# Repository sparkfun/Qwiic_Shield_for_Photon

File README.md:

SparkFun Qwiic Shield for Photon
========================================

[*Qwiic Shield for Photon*](https://www.sparkfun.com/products/14477)

This is a board that connects the I<sup>2</sup>C bus on the Photon to 4 Qwiic connectors.

Repository Contents
-------------------

* **/Hardware** - Eagle design files (.brd, .sch)
* **/Production** - Production panel files (.brd)

Documentation
--------------
* **[Hookup Guide](https://learn.sparkfun.com/tutorials/qwiic-shield-for-arduino--photon-hookup-guide)** - Basic hookup guide for the Qwiic Shield for Photon.

License Information
-------------------

This product is _**open source**_! 

Please review the LICENSE.md file for license information. 

If you have any questions or concerns on licensing, please contact techsupport@sparkfun.com.

Distributed as-is; no warranty is given.

- Your friends at SparkFun.

_<COLLABORATION CREDIT>_

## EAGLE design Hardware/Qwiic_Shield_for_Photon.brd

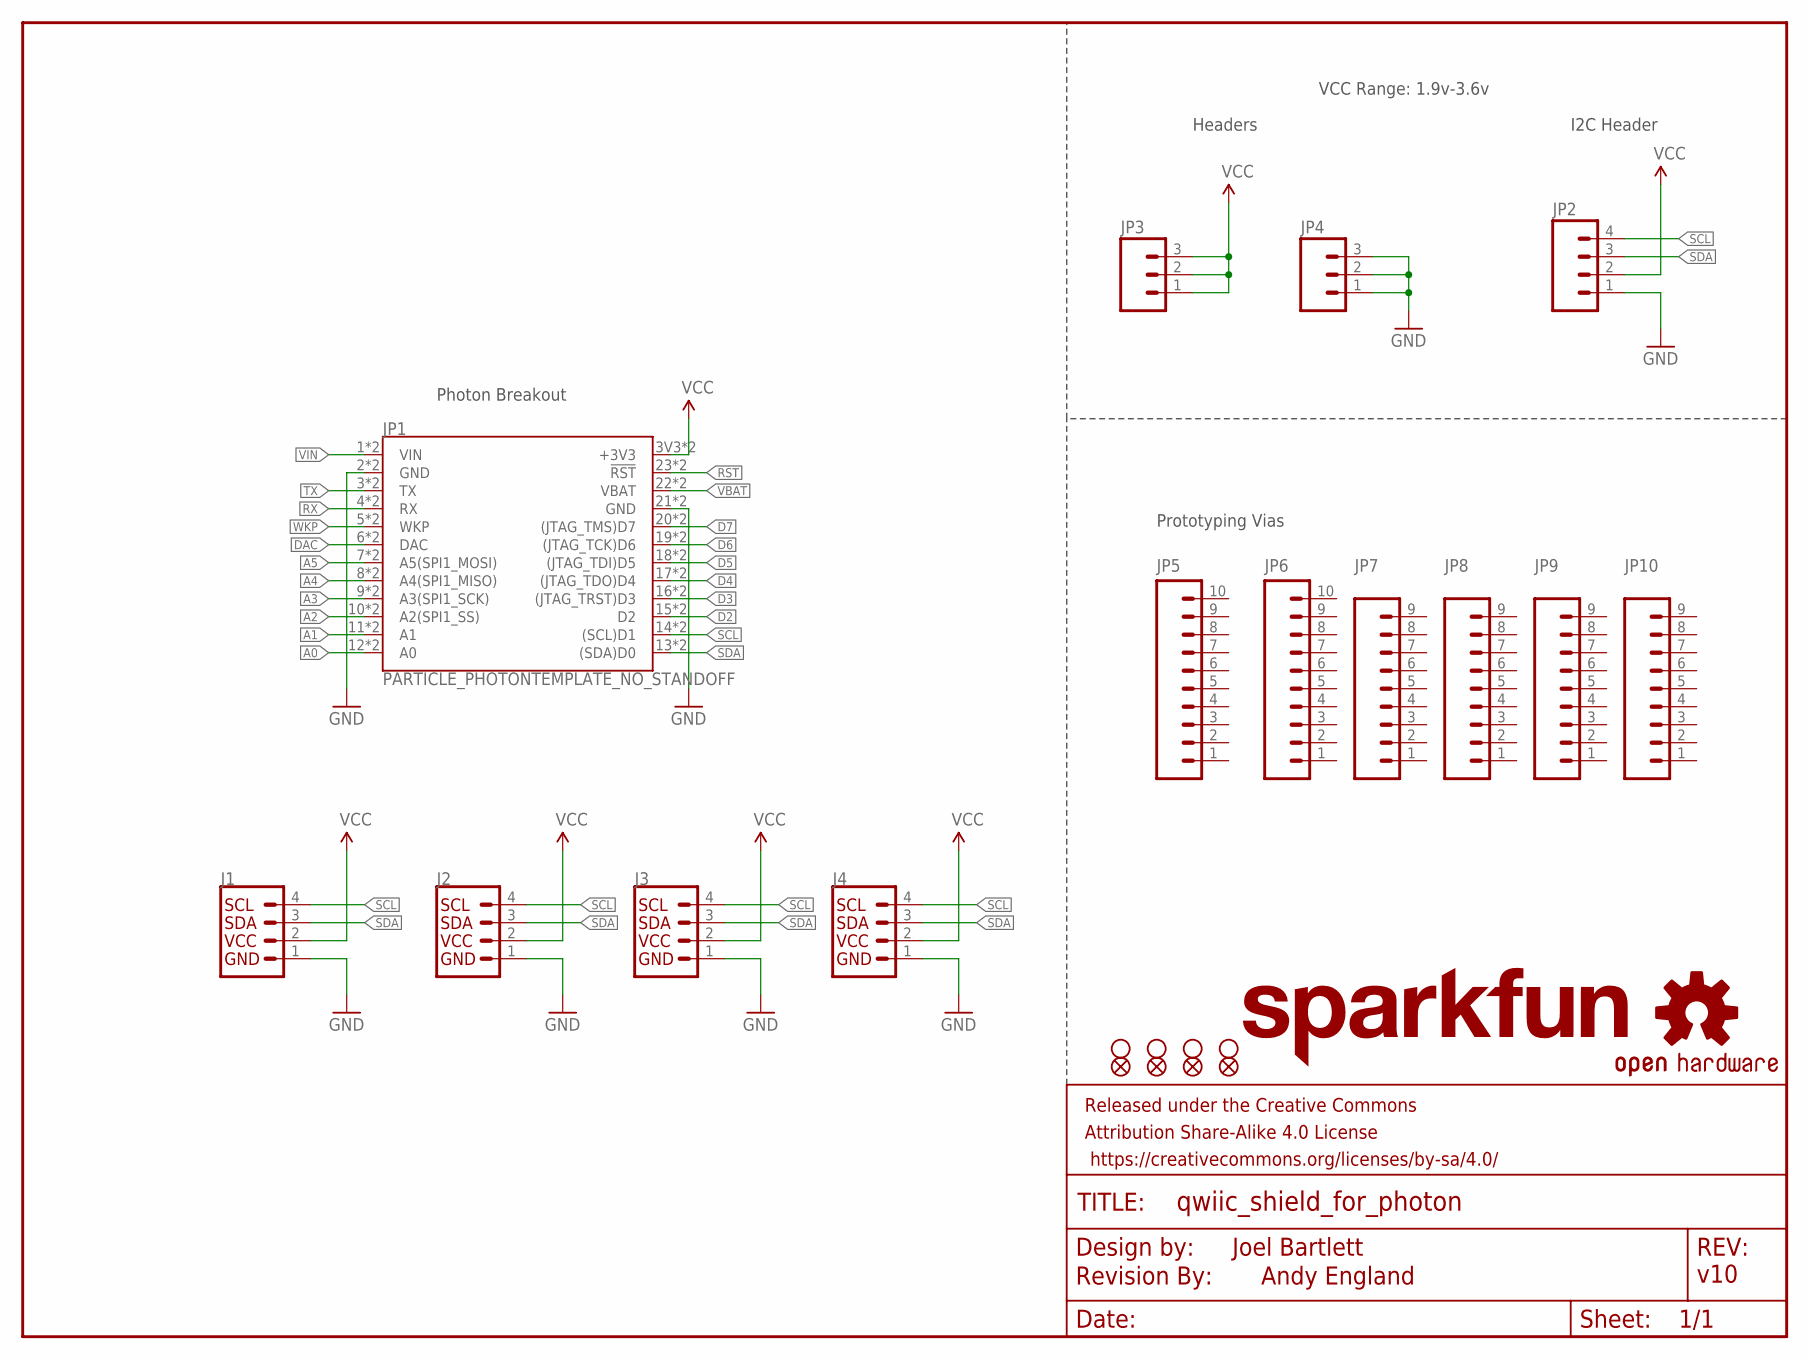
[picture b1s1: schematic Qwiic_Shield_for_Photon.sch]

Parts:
FD1, FD2, FD3, FD4: FIDUCIALUFIDUCIAL; FIDUCIAL-MICRO
FRAME1: FRAME-LETTER; CREATIVE_COMMONS
H1, H2, H3, H4: STAND-OFF
J1, J2, J3: QWIIC_CONNECTORJS-1MM; 1X04_1MM_RA
J4: I2C_STANDARDJS-1MM; 1X04_1MM_RA
JP1: PARTICLE_PHOTONTEMPLATE_NO_STANDOFF; PARTICLE_PHOTON_TEMPLATE_NO_STANDOFF
JP2: M04PTH; 1X04
JP3, JP4: M03PTH; 1X03
JP5, JP6: M10NO_SILK_PTH_FEMALE; 1X10_NO_SILK
JP7, JP8, JP9, JP10: M09NO_SILK; 1X09_NO_SILK
LOGO1: OSHW-LOGOM; OSHW-LOGO-M
LOGO2: REVISION
U$4: SFE_LOGO_NAME.1_INCH; SFE_LOGO_NAME_.1

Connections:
A0: JP1.12 (A0), JP1.A0
A1: JP1.11 (A1), JP1.A1
A2: JP1.10 (A2(SPI1_SS)), JP1.A2 (A2(SPI1_SS))
A3: JP1.9 (A3(SPI1_SCK)), JP1.A3 (A3(SPI1_SCK))
A4: JP1.8 (A4(SPI1_MISO)), JP1.A4 (A4(SPI1_MISO))
A5: JP1.7 (A5(SPI1_MOSI)), JP1.A5 (A5(SPI1_MOSI))
D2: JP1.15 (D2), JP1.D2
D3: JP1.16 ((JTAG_TRST)D3), JP1.D3 ((JTAG_TRST)D3)
D4: JP1.17 ((JTAG_TDO)D4), JP1.D4 ((JTAG_TDO)D4)
D5: JP1.18 ((JTAG_TDI)D5), JP1.D5 ((JTAG_TDI)D5)
D6: JP1.19 ((JTAG_TCK)D6), JP1.D6 ((JTAG_TCK)D6)
D7: JP1.20 ((JTAG_TMS)D7), JP1.D7 ((JTAG_TMS)D7)
DAC: JP1.6 (DAC), JP1.DAC
GND: J1.1 (GND), J2.1 (GND), J3.1 (GND), J4.1 (GND), JP1.2 (GND), JP1.21 (GND), JP1.GND@0 (GND), JP1.GND@2 (GND), JP2.1, JP4.1, JP4.2, JP4.3
RST: JP1.23 (!RST!), JP1.RST (!RST!)
RX: JP1.4 (RX), JP1.RX
SCL: J1.4 (SCL), J2.4 (SCL), J3.4 (SCL), J4.4 (SCL), JP1.14 ((SCL)D1), JP1.D1 ((SCL)D1), JP2.4
SDA: J1.3 (SDA), J2.3 (SDA), J3.3 (SDA), J4.3 (SDA), JP1.13 ((SDA)D0), JP1.D0 ((SDA)D0), JP2.3
TX: JP1.3 (TX), JP1.TX
VBAT: JP1.22 (VBAT), JP1.VBAT
VCC: J1.2 (VCC), J2.2 (VCC), J3.2 (VCC), J4.2 (VCC), JP1.3V3 (+3V3), JP1.24 (+3V3), JP2.2, JP3.1, JP3.2, JP3.3
VIN: JP1.1 (VIN), JP1.VIN
WKP: JP1.5 (WKP), JP1.WKP

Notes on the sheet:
I2C Header
Prototyping Vias
Headers
Photon Breakout
VCC Range: 1.9v-3.6v
Joel Bartlett
Andy England
v10

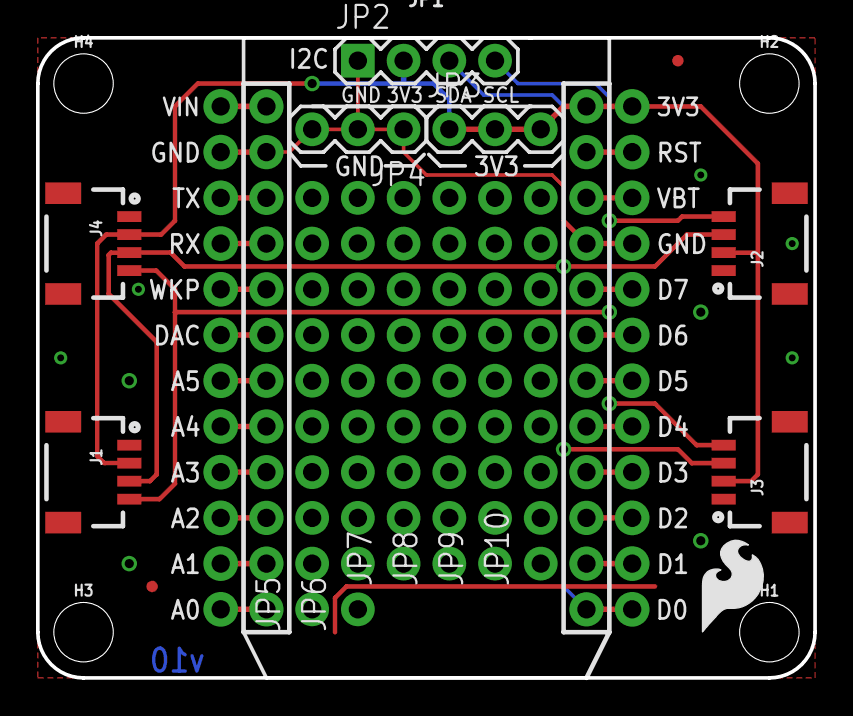
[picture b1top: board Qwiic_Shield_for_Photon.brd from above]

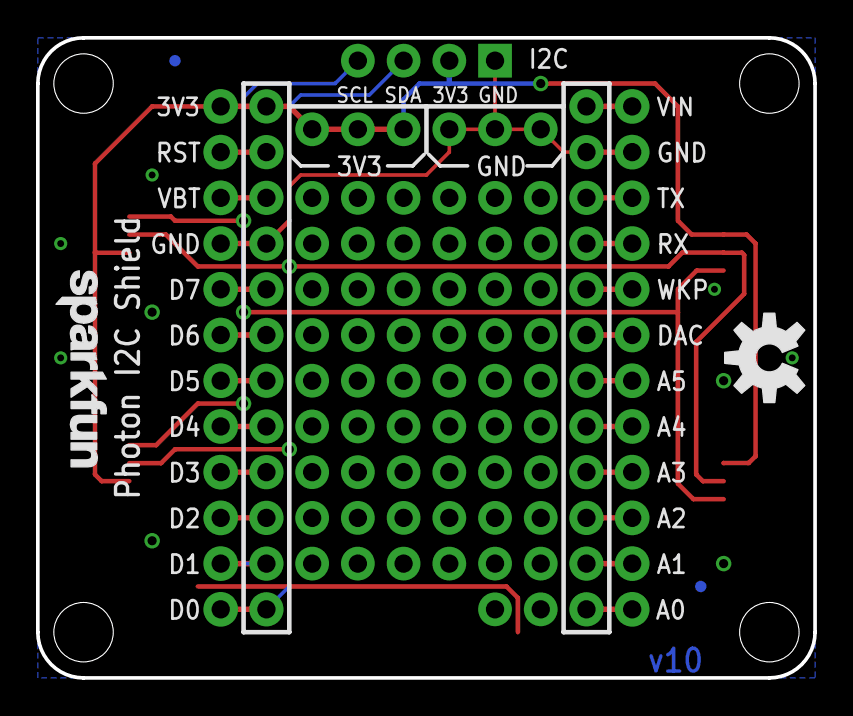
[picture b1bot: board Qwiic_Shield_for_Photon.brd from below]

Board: 2 copper layers, 43.2 x 35.6 mm, 27 parts (4 on the bottom side), 23 nets.

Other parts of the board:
U$1: SFE_LOGO_FLAME_.2

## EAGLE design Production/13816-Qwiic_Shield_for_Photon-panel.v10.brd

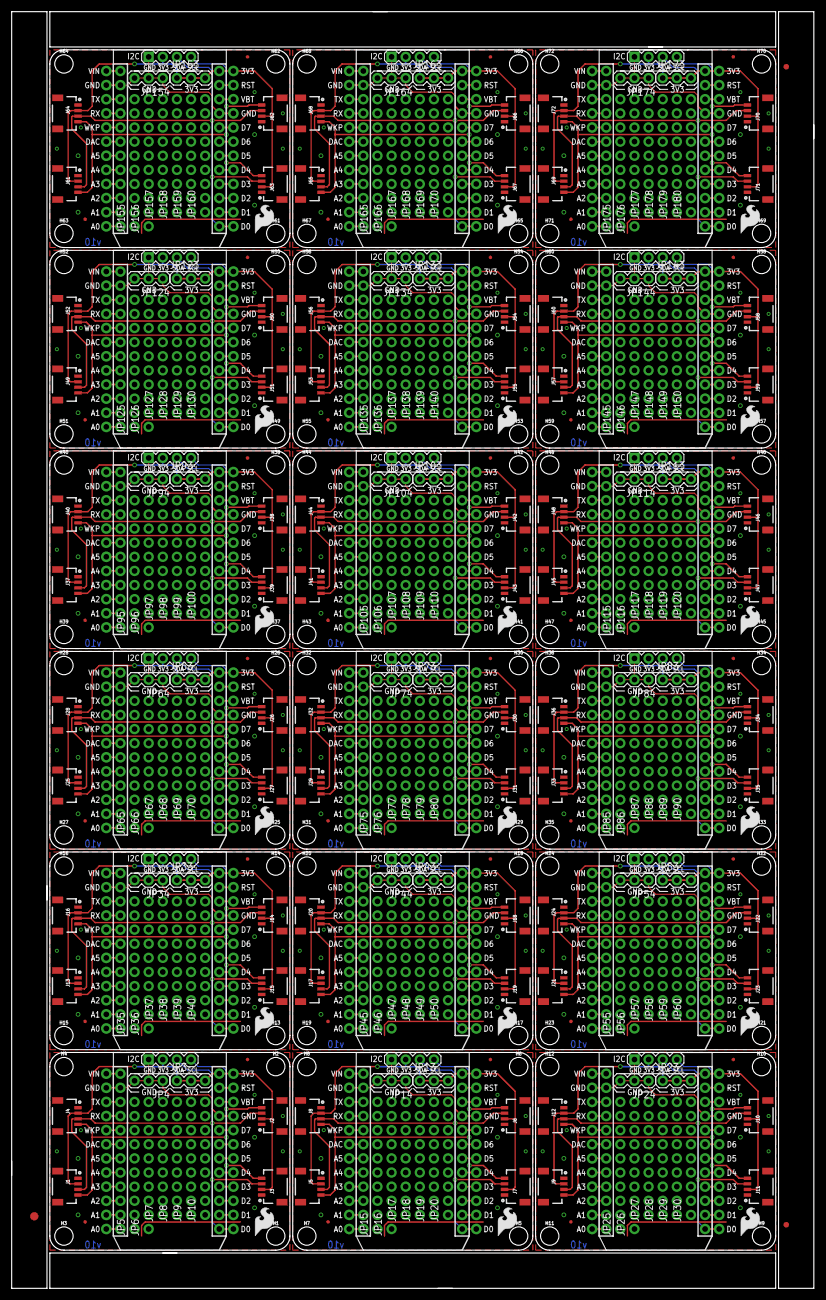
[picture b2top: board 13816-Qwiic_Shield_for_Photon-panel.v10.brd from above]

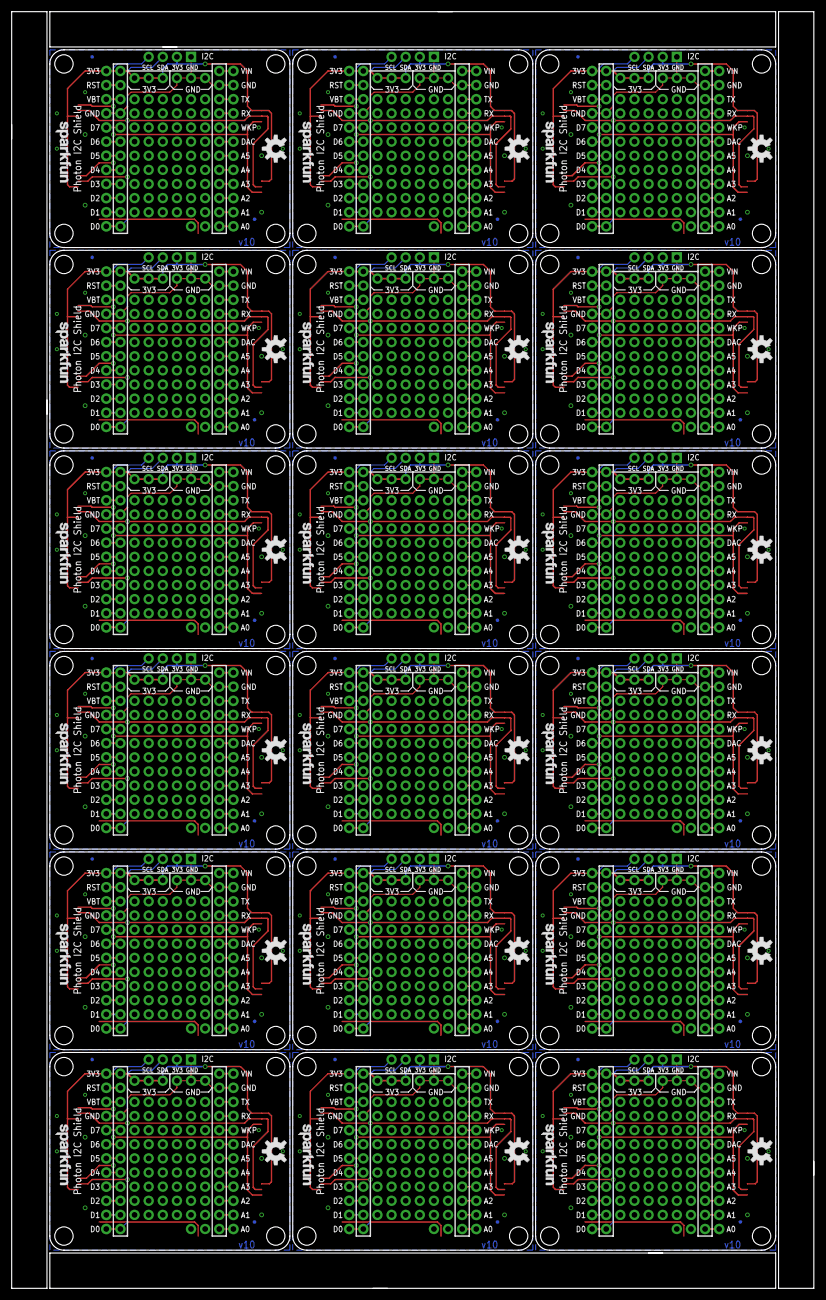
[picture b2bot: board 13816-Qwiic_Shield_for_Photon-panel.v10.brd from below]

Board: 2 copper layers, 144.3 x 229.6 mm, 453 parts (72 on the bottom side), 414 nets.

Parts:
E$1: FIDUCIAL-1.5X3
E$7, E$8: FIDUCIAL-1X2
FD1, FD2, FD3, FD4, FD5, FD6, FD7, FD8, FD9, FD10, FD11, FD12, FD13, FD14, FD15, FD16, FD17, FD18, FD19, FD20, FD21, FD22, FD23, FD24, FD25, FD26, FD27, FD28, FD29, FD30, FD31, FD32, FD33, FD34, FD35, FD36, FD37, FD38, FD39, FD40, FD41, FD42, FD43, FD44, FD45, FD46, FD47, FD48, FD49, FD50, FD51, FD52, FD53, FD54, FD55, FD56, FD57, FD58, FD59, FD60, FD61, FD62, FD63, FD64, FD65, FD66, FD67, FD68, FD69, FD70, FD71, FD72: FIDUCIALUFIDUCIAL; FIDUCIAL-MICRO
H1, H2, H3, H4, H5, H6, H7, H8, H9, H10, H11, H12, H13, H14, H15, H16, H17, H18, H19, H20, H21, H22, H23, H24, H25, H26, H27, H28, H29, H30, H31, H32, H33, H34, H35, H36, H37, H38, H39, H40, H41, H42, H43, H44, H45, H46, H47, H48, H49, H50, H51, H52, H53, H54, H55, H56, H57, H58, H59, H60, H61, H62, H63, H64, H65, H66, H67, H68, H69, H70, H71, H72: STAND-OFF
J1, J2, J3, J4, J5, J6, J7, J8, J9, J10, J11, J12, J13, J14, J15, J16, J17, J18, J19, J20, J21, J22, J23, J24, J25, J26, J27, J28, J29, J30, J31, J32, J33, J34, J35, J36, J37, J38, J39, J40, J41, J42, J43, J44, J45, J46, J47, J48, J49, J50, J51, J52, J53, J54, J55, J56, J57, J58, J59, J60, J61, J62, J63, J64, J65, J66, J67, J68, J69, J70, J71, J72: 1X04_1MM_RA
JP1, JP11, JP21, JP31, JP41, JP51, JP61, JP71, JP81, JP91, JP101, JP111, JP121, JP131, JP141, JP151, JP161, JP171: PARTICLE_PHOTONTEMPLATE_NO_STANDOFF; PARTICLE_PHOTON_TEMPLATE_NO_STANDOFF
JP2, JP12, JP22, JP32, JP42, JP52, JP62, JP72, JP82, JP92, JP102, JP112, JP122, JP132, JP142, JP152, JP162, JP172: 1X04
JP3, JP4, JP13, JP14, JP23, JP24, JP33, JP34, JP43, JP44, JP53, JP54, JP63, JP64, JP73, JP74, JP83, JP84, JP93, JP94, JP103, JP104, JP113, JP114, JP123, JP124, JP133, JP134, JP143, JP144, JP153, JP154, JP163, JP164, JP173, JP174: 1X03
JP5, JP6, JP15, JP16, JP25, JP26, JP35, JP36, JP45, JP46, JP55, JP56, JP65, JP66, JP75, JP76, JP85, JP86, JP95, JP96, JP105, JP106, JP115, JP116, JP125, JP126, JP135, JP136, JP145, JP146, JP155, JP156, JP165, JP166, JP175, JP176: 1X10_NO_SILK
JP7, JP8, JP9, JP10, JP17, JP18, JP19, JP20, JP27, JP28, JP29, JP30, JP37, JP38, JP39, JP40, JP47, JP48, JP49, JP50, JP57, JP58, JP59, JP60, JP67, JP68, JP69, JP70, JP77, JP78, JP79, JP80, JP87, JP88, JP89, JP90, JP97, JP98, JP99, JP100, JP107, JP108, JP109, JP110, JP117, JP118, JP119, JP120, JP127, JP128, JP129, JP130, JP137, JP138, JP139, JP140, JP147, JP148, JP149, JP150, JP157, JP158, JP159, JP160, JP167, JP168, JP169, JP170, JP177, JP178, JP179, JP180: 1X09_NO_SILK
LOGO1, LOGO2, LOGO3, LOGO4, LOGO5, LOGO6, LOGO7, LOGO8, LOGO9, LOGO10, LOGO11, LOGO12, LOGO13, LOGO14, LOGO15, LOGO16, LOGO17, LOGO18: OSHW-LOGOM; OSHW-LOGO-M
U$1, U$2, U$5, U$7, U$9, U$11, U$13, U$15, U$17, U$19, U$21, U$23, U$25, U$27, U$29, U$31, U$33, U$35: SFE_LOGO_FLAME_.2
U$3, U$4, U$6, U$8, U$10, U$12, U$14, U$16, U$18, U$20, U$22, U$24, U$26, U$28, U$30, U$32, U$34, U$36: SFE_LOGO_NAME.1_INCH; SFE_LOGO_NAME_.1

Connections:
A0: JP1.12, JP1.A0
A1: JP1.11, JP1.A1
A2: JP1.10, JP1.A2
A3: JP1.9, JP1.A3
A4: JP1.8, JP1.A4
A5: JP1.7, JP1.A5
A6: JP11.7, JP11.A5
A7: JP11.8, JP11.A4
A8: JP11.9, JP11.A3
A9: JP11.10, JP11.A2
A10: JP11.11, JP11.A1
A11: JP11.12, JP11.A0
A12: JP21.7, JP21.A5
A13: JP21.8, JP21.A4
A14: JP21.9, JP21.A3
A15: JP21.10, JP21.A2
A16: JP21.11, JP21.A1
A17: JP21.12, JP21.A0
A18: JP31.7, JP31.A5
A19: JP31.8, JP31.A4
A20: JP31.9, JP31.A3
A21: JP31.10, JP31.A2
A22: JP31.11, JP31.A1
A23: JP31.12, JP31.A0
A24: JP41.7, JP41.A5
A25: JP41.8, JP41.A4
A26: JP41.9, JP41.A3
A27: JP41.10, JP41.A2
A28: JP41.11, JP41.A1
A29: JP41.12, JP41.A0
A30: JP51.7, JP51.A5
A31: JP51.8, JP51.A4
A32: JP51.9, JP51.A3
A33: JP51.10, JP51.A2
A34: JP51.11, JP51.A1
A35: JP51.12, JP51.A0
A36: JP61.7, JP61.A5
A37: JP61.8, JP61.A4
A38: JP61.9, JP61.A3
A39: JP61.10, JP61.A2
A40: JP61.11, JP61.A1
A41: JP61.12, JP61.A0
A42: JP71.7, JP71.A5
A43: JP71.8, JP71.A4
A44: JP71.9, JP71.A3
A45: JP71.10, JP71.A2
A46: JP71.11, JP71.A1
A47: JP71.12, JP71.A0
A48: JP81.7, JP81.A5
A49: JP81.8, JP81.A4
A50: JP81.9, JP81.A3
A51: JP81.10, JP81.A2
A52: JP81.11, JP81.A1
A53: JP81.12, JP81.A0
A54: JP91.7, JP91.A5
A55: JP91.8, JP91.A4
A56: JP91.9, JP91.A3
A57: JP91.10, JP91.A2
A58: JP91.11, JP91.A1
A59: JP91.12, JP91.A0
A60: JP101.7, JP101.A5
A61: JP101.8, JP101.A4
A62: JP101.9, JP101.A3
A63: JP101.10, JP101.A2
A64: JP101.11, JP101.A1
A65: JP101.12, JP101.A0
A66: JP111.7, JP111.A5
A67: JP111.8, JP111.A4
A68: JP111.9, JP111.A3
A69: JP111.10, JP111.A2
A70: JP111.11, JP111.A1
A71: JP111.12, JP111.A0
A72: JP121.7, JP121.A5
A73: JP121.8, JP121.A4
A74: JP121.9, JP121.A3
A75: JP121.10, JP121.A2
A76: JP121.11, JP121.A1
A77: JP121.12, JP121.A0
A78: JP131.7, JP131.A5
A79: JP131.8, JP131.A4
A80: JP131.9, JP131.A3
A81: JP131.10, JP131.A2
A82: JP131.11, JP131.A1
A83: JP131.12, JP131.A0
A84: JP141.7, JP141.A5
A85: JP141.8, JP141.A4
A86: JP141.9, JP141.A3
A87: JP141.10, JP141.A2
A88: JP141.11, JP141.A1
A89: JP141.12, JP141.A0
A90: JP151.7, JP151.A5
A91: JP151.8, JP151.A4
A92: JP151.9, JP151.A3
A93: JP151.10, JP151.A2
A94: JP151.11, JP151.A1
A95: JP151.12, JP151.A0
A96: JP161.7, JP161.A5
A97: JP161.8, JP161.A4
A98: JP161.9, JP161.A3
A99: JP161.10, JP161.A2
A100: JP161.11, JP161.A1
A101: JP161.12, JP161.A0
A102: JP171.7, JP171.A5
A103: JP171.8, JP171.A4
A104: JP171.9, JP171.A3
A105: JP171.10, JP171.A2
A106: JP171.11, JP171.A1
A107: JP171.12, JP171.A0
D1: JP11.20, JP11.D7
D2: JP1.15, JP1.D2
D3: JP1.16, JP1.D3
D4: JP1.17, JP1.D4
D5: JP1.18, JP1.D5
D6: JP1.19, JP1.D6
D7: JP1.20, JP1.D7
D8: JP11.19, JP11.D6
D9: JP11.18, JP11.D5
D10: JP11.17, JP11.D4
D11: JP11.16, JP11.D3
D12: JP11.15, JP11.D2
D13: JP21.20, JP21.D7
D14: JP21.19, JP21.D6
D15: JP21.18, JP21.D5
D16: JP21.17, JP21.D4
D17: JP21.16, JP21.D3
D18: JP21.15, JP21.D2
D19: JP31.20, JP31.D7
D20: JP31.19, JP31.D6
D21: JP31.18, JP31.D5
D22: JP31.17, JP31.D4
D23: JP31.16, JP31.D3
D24: JP31.15, JP31.D2
D25: JP41.20, JP41.D7
D26: JP41.19, JP41.D6
D27: JP41.18, JP41.D5
D28: JP41.17, JP41.D4
D29: JP41.16, JP41.D3
D30: JP41.15, JP41.D2
D31: JP51.20, JP51.D7
D32: JP51.19, JP51.D6
D33: JP51.18, JP51.D5
D34: JP51.17, JP51.D4
D35: JP51.16, JP51.D3
D36: JP51.15, JP51.D2
D37: JP61.20, JP61.D7
D38: JP61.19, JP61.D6
D39: JP61.18, JP61.D5
D40: JP61.17, JP61.D4
D41: JP61.16, JP61.D3
D42: JP61.15, JP61.D2
D43: JP71.20, JP71.D7
D44: JP71.19, JP71.D6
D45: JP71.18, JP71.D5
D46: JP71.17, JP71.D4
D47: JP71.16, JP71.D3
D48: JP71.15, JP71.D2
D49: JP81.20, JP81.D7
D50: JP81.19, JP81.D6
D51: JP81.18, JP81.D5
D52: JP81.17, JP81.D4
D53: JP81.16, JP81.D3
D54: JP81.15, JP81.D2
D55: JP91.20, JP91.D7
D56: JP91.19, JP91.D6
D57: JP91.18, JP91.D5
D58: JP91.17, JP91.D4
D59: JP91.16, JP91.D3
D60: JP91.15, JP91.D2
D61: JP101.20, JP101.D7
D62: JP101.19, JP101.D6
D63: JP101.18, JP101.D5
D64: JP101.17, JP101.D4
D65: JP101.16, JP101.D3
D66: JP101.15, JP101.D2
D67: JP111.20, JP111.D7
D68: JP111.19, JP111.D6
D69: JP111.18, JP111.D5
D70: JP111.17, JP111.D4
D71: JP111.16, JP111.D3
D72: JP111.15, JP111.D2
D73: JP121.20, JP121.D7
D74: JP121.19, JP121.D6
D75: JP121.18, JP121.D5
D76: JP121.17, JP121.D4
D77: JP121.16, JP121.D3
D78: JP121.15, JP121.D2
D79: JP131.20, JP131.D7
D80: JP131.19, JP131.D6
D81: JP131.18, JP131.D5
D82: JP131.17, JP131.D4
D83: JP131.16, JP131.D3
D84: JP131.15, JP131.D2
D85: JP141.20, JP141.D7
D86: JP141.19, JP141.D6
D87: JP141.18, JP141.D5
D88: JP141.17, JP141.D4
D89: JP141.16, JP141.D3
D90: JP141.15, JP141.D2
D91: JP151.20, JP151.D7
D92: JP151.19, JP151.D6
D93: JP151.18, JP151.D5
D94: JP151.17, JP151.D4
D95: JP151.16, JP151.D3
D96: JP151.15, JP151.D2
D97: JP161.20, JP161.D7
D98: JP161.19, JP161.D6
D99: JP161.18, JP161.D5
D100: JP161.17, JP161.D4
D101: JP161.16, JP161.D3
D102: JP161.15, JP161.D2
D103: JP171.20, JP171.D7
D104: JP171.19, JP171.D6
D105: JP171.18, JP171.D5
D106: JP171.17, JP171.D4
D107: JP171.16, JP171.D3
D108: JP171.15, JP171.D2
DAC: JP1.6, JP1.DAC
DAC1: JP11.6, JP11.DAC
DAC2: JP21.6, JP21.DAC
DAC3: JP31.6, JP31.DAC
DAC4: JP41.6, JP41.DAC
DAC5: JP51.6, JP51.DAC
DAC6: JP61.6, JP61.DAC
DAC7: JP71.6, JP71.DAC
DAC8: JP81.6, JP81.DAC
DAC9: JP91.6, JP91.DAC
DAC10: JP101.6, JP101.DAC
DAC11: JP111.6, JP111.DAC
DAC12: JP121.6, JP121.DAC
DAC13: JP131.6, JP131.DAC
DAC14: JP141.6, JP141.DAC
DAC15: JP151.6, JP151.DAC
DAC16: JP161.6, JP161.DAC
DAC17: JP171.6, JP171.DAC
GND: J1.1, J2.1, J3.1, J4.1, JP1.2, JP1.21, JP1.GND@0, JP1.GND@2, JP2.1, JP4.1, JP4.2, JP4.3
GND1: J5.1, J6.1, J7.1, J8.1, JP11.2, JP11.21, JP11.GND@0, JP11.GND@2, JP12.1, JP14.1, JP14.2, JP14.3
GND2: J9.1, J10.1, J11.1, J12.1, JP21.2, JP21.21, JP21.GND@0, JP21.GND@2, JP22.1, JP24.1, JP24.2, JP24.3
GND3: J13.1, J14.1, J15.1, J16.1, JP31.2, JP31.21, JP31.GND@0, JP31.GND@2, JP32.1, JP34.1, JP34.2, JP34.3
GND4: J17.1, J18.1, J19.1, J20.1, JP41.2, JP41.21, JP41.GND@0, JP41.GND@2, JP42.1, JP44.1, JP44.2, JP44.3
GND5: J21.1, J22.1, J23.1, J24.1, JP51.2, JP51.21, JP51.GND@0, JP51.GND@2, JP52.1, JP54.1, JP54.2, JP54.3
GND6: J25.1, J26.1, J27.1, J28.1, JP61.2, JP61.21, JP61.GND@0, JP61.GND@2, JP62.1, JP64.1, JP64.2, JP64.3
GND7: J29.1, J30.1, J31.1, J32.1, JP71.2, JP71.21, JP71.GND@0, JP71.GND@2, JP72.1, JP74.1, JP74.2, JP74.3
GND8: J33.1, J34.1, J35.1, J36.1, JP81.2, JP81.21, JP81.GND@0, JP81.GND@2, JP82.1, JP84.1, JP84.2, JP84.3
GND9: J37.1, J38.1, J39.1, J40.1, JP91.2, JP91.21, JP91.GND@0, JP91.GND@2, JP92.1, JP94.1, JP94.2, JP94.3
GND10: J41.1, J42.1, J43.1, J44.1, JP101.2, JP101.21, JP101.GND@0, JP101.GND@2, JP102.1, JP104.1, JP104.2, JP104.3
GND11: J45.1, J46.1, J47.1, J48.1, JP111.2, JP111.21, JP111.GND@0, JP111.GND@2, JP112.1, JP114.1, JP114.2, JP114.3
GND12: J49.1, J50.1, J51.1, J52.1, JP121.2, JP121.21, JP121.GND@0, JP121.GND@2, JP122.1, JP124.1, JP124.2, JP124.3
GND13: J53.1, J54.1, J55.1, J56.1, JP131.2, JP131.21, JP131.GND@0, JP131.GND@2, JP132.1, JP134.1, JP134.2, JP134.3
GND14: J57.1, J58.1, J59.1, J60.1, JP141.2, JP141.21, JP141.GND@0, JP141.GND@2, JP142.1, JP144.1, JP144.2, JP144.3
GND15: J61.1, J62.1, J63.1, J64.1, JP151.2, JP151.21, JP151.GND@0, JP151.GND@2, JP152.1, JP154.1, JP154.2, JP154.3
GND16: J65.1, J66.1, J67.1, J68.1, JP161.2, JP161.21, JP161.GND@0, JP161.GND@2, JP162.1, JP164.1, JP164.2, JP164.3
GND17: J69.1, J70.1, J71.1, J72.1, JP171.2, JP171.21, JP171.GND@0, JP171.GND@2, JP172.1, JP174.1, JP174.2, JP174.3
RST: JP1.23, JP1.RST
RST1: JP11.23, JP11.RST
RST2: JP21.23, JP21.RST
RST3: JP31.23, JP31.RST
RST4: JP41.23, JP41.RST
RST5: JP51.23, JP51.RST
RST6: JP61.23, JP61.RST
RST7: JP71.23, JP71.RST
RST8: JP81.23, JP81.RST
RST9: JP91.23, JP91.RST
RST10: JP101.23, JP101.RST
RST11: JP111.23, JP111.RST
RST12: JP121.23, JP121.RST
RST13: JP131.23, JP131.RST
RST14: JP141.23, JP141.RST
RST15: JP151.23, JP151.RST
RST16: JP161.23, JP161.RST
RST17: JP171.23, JP171.RST
RX: JP1.4, JP1.RX
RX1: JP11.4, JP11.RX
RX2: JP21.4, JP21.RX
RX3: JP31.4, JP31.RX
RX4: JP41.4, JP41.RX
RX5: JP51.4, JP51.RX
RX6: JP61.4, JP61.RX
RX7: JP71.4, JP71.RX
RX8: JP81.4, JP81.RX
RX9: JP91.4, JP91.RX
RX10: JP101.4, JP101.RX
RX11: JP111.4, JP111.RX
RX12: JP121.4, JP121.RX
RX13: JP131.4, JP131.RX
RX14: JP141.4, JP141.RX
RX15: JP151.4, JP151.RX
RX16: JP161.4, JP161.RX
RX17: JP171.4, JP171.RX
SCL: J1.4, J2.4, J3.4, J4.4, JP1.14, JP1.D1, JP2.4
SCL1: J5.4, J6.4, J7.4, J8.4, JP11.14, JP11.D1, JP12.4
SCL2: J9.4, J10.4, J11.4, J12.4, JP21.14, JP21.D1, JP22.4
SCL3: J13.4, J14.4, J15.4, J16.4, JP31.14, JP31.D1, JP32.4
SCL4: J17.4, J18.4, J19.4, J20.4, JP41.14, JP41.D1, JP42.4
SCL5: J21.4, J22.4, J23.4, J24.4, JP51.14, JP51.D1, JP52.4
SCL6: J25.4, J26.4, J27.4, J28.4, JP61.14, JP61.D1, JP62.4
SCL7: J29.4, J30.4, J31.4, J32.4, JP71.14, JP71.D1, JP72.4
SCL8: J33.4, J34.4, J35.4, J36.4, JP81.14, JP81.D1, JP82.4
SCL9: J37.4, J38.4, J39.4, J40.4, JP91.14, JP91.D1, JP92.4
SCL10: J41.4, J42.4, J43.4, J44.4, JP101.14, JP101.D1, JP102.4
SCL11: J45.4, J46.4, J47.4, J48.4, JP111.14, JP111.D1, JP112.4
SCL12: J49.4, J50.4, J51.4, J52.4, JP121.14, JP121.D1, JP122.4
SCL13: J53.4, J54.4, J55.4, J56.4, JP131.14, JP131.D1, JP132.4
SCL14: J57.4, J58.4, J59.4, J60.4, JP141.14, JP141.D1, JP142.4
SCL15: J61.4, J62.4, J63.4, J64.4, JP151.14, JP151.D1, JP152.4
SCL16: J65.4, J66.4, J67.4, J68.4, JP161.14, JP161.D1, JP162.4
SCL17: J69.4, J70.4, J71.4, J72.4, JP171.14, JP171.D1, JP172.4
SDA: J1.3, J2.3, J3.3, J4.3, JP1.13, JP1.D0, JP2.3
SDA1: J5.3, J6.3, J7.3, J8.3, JP11.13, JP11.D0, JP12.3
SDA2: J9.3, J10.3, J11.3, J12.3, JP21.13, JP21.D0, JP22.3
SDA3: J13.3, J14.3, J15.3, J16.3, JP31.13, JP31.D0, JP32.3
SDA4: J17.3, J18.3, J19.3, J20.3, JP41.13, JP41.D0, JP42.3
SDA5: J21.3, J22.3, J23.3, J24.3, JP51.13, JP51.D0, JP52.3
SDA6: J25.3, J26.3, J27.3, J28.3, JP61.13, JP61.D0, JP62.3
SDA7: J29.3, J30.3, J31.3, J32.3, JP71.13, JP71.D0, JP72.3
SDA8: J33.3, J34.3, J35.3, J36.3, JP81.13, JP81.D0, JP82.3
SDA9: J37.3, J38.3, J39.3, J40.3, JP91.13, JP91.D0, JP92.3
SDA10: J41.3, J42.3, J43.3, J44.3, JP101.13, JP101.D0, JP102.3
SDA11: J45.3, J46.3, J47.3, J48.3, JP111.13, JP111.D0, JP112.3
SDA12: J49.3, J50.3, J51.3, J52.3, JP121.13, JP121.D0, JP122.3
SDA13: J53.3, J54.3, J55.3, J56.3, JP131.13, JP131.D0, JP132.3
SDA14: J57.3, J58.3, J59.3, J60.3, JP141.13, JP141.D0, JP142.3
SDA15: J61.3, J62.3, J63.3, J64.3, JP151.13, JP151.D0, JP152.3
SDA16: J65.3, J66.3, J67.3, J68.3, JP161.13, JP161.D0, JP162.3
SDA17: J69.3, J70.3, J71.3, J72.3, JP171.13, JP171.D0, JP172.3
TX: JP1.3, JP1.TX
TX1: JP11.3, JP11.TX
TX2: JP21.3, JP21.TX
TX3: JP31.3, JP31.TX
TX4: JP41.3, JP41.TX
TX5: JP51.3, JP51.TX
TX6: JP61.3, JP61.TX
TX7: JP71.3, JP71.TX
TX8: JP81.3, JP81.TX
TX9: JP91.3, JP91.TX
TX10: JP101.3, JP101.TX
TX11: JP111.3, JP111.TX
TX12: JP121.3, JP121.TX
TX13: JP131.3, JP131.TX
TX14: JP141.3, JP141.TX
TX15: JP151.3, JP151.TX
TX16: JP161.3, JP161.TX
TX17: JP171.3, JP171.TX
VBAT: JP1.22, JP1.VBAT
VBAT1: JP11.22, JP11.VBAT
VBAT2: JP21.22, JP21.VBAT
VBAT3: JP31.22, JP31.VBAT
VBAT4: JP41.22, JP41.VBAT
VBAT5: JP51.22, JP51.VBAT
VBAT6: JP61.22, JP61.VBAT
VBAT7: JP71.22, JP71.VBAT
VBAT8: JP81.22, JP81.VBAT
VBAT9: JP91.22, JP91.VBAT
VBAT10: JP101.22, JP101.VBAT
VBAT11: JP111.22, JP111.VBAT
VBAT12: JP121.22, JP121.VBAT
VBAT13: JP131.22, JP131.VBAT
VBAT14: JP141.22, JP141.VBAT
VBAT15: JP151.22, JP151.VBAT
VBAT16: JP161.22, JP161.VBAT
VBAT17: JP171.22, JP171.VBAT
VCC: J1.2, J2.2, J3.2, J4.2, JP1.3V3, JP1.24, JP2.2, JP3.1, JP3.2, JP3.3
VCC1: J5.2, J6.2, J7.2, J8.2, JP11.3V3, JP11.24, JP12.2, JP13.1, JP13.2, JP13.3
VCC2: J9.2, J10.2, J11.2, J12.2, JP21.3V3, JP21.24, JP22.2, JP23.1, JP23.2, JP23.3
VCC3: J13.2, J14.2, J15.2, J16.2, JP31.3V3, JP31.24, JP32.2, JP33.1, JP33.2, JP33.3
VCC4: J17.2, J18.2, J19.2, J20.2, JP41.3V3, JP41.24, JP42.2, JP43.1, JP43.2, JP43.3
VCC5: J21.2, J22.2, J23.2, J24.2, JP51.3V3, JP51.24, JP52.2, JP53.1, JP53.2, JP53.3
VCC6: J25.2, J26.2, J27.2, J28.2, JP61.3V3, JP61.24, JP62.2, JP63.1, JP63.2, JP63.3
VCC7: J29.2, J30.2, J31.2, J32.2, JP71.3V3, JP71.24, JP72.2, JP73.1, JP73.2, JP73.3
VCC8: J33.2, J34.2, J35.2, J36.2, JP81.3V3, JP81.24, JP82.2, JP83.1, JP83.2, JP83.3
VCC9: J37.2, J38.2, J39.2, J40.2, JP91.3V3, JP91.24, JP92.2, JP93.1, JP93.2, JP93.3
VCC10: J41.2, J42.2, J43.2, J44.2, JP101.3V3, JP101.24, JP102.2, JP103.1, JP103.2, JP103.3
VCC11: J45.2, J46.2, J47.2, J48.2, JP111.3V3, JP111.24, JP112.2, JP113.1, JP113.2, JP113.3
VCC12: J49.2, J50.2, J51.2, J52.2, JP121.3V3, JP121.24, JP122.2, JP123.1, JP123.2, JP123.3
VCC13: J53.2, J54.2, J55.2, J56.2, JP131.3V3, JP131.24, JP132.2, JP133.1, JP133.2, JP133.3
VCC14: J57.2, J58.2, J59.2, J60.2, JP141.3V3, JP141.24, JP142.2, JP143.1, JP143.2, JP143.3
VCC15: J61.2, J62.2, J63.2, J64.2, JP151.3V3, JP151.24, JP152.2, JP153.1, JP153.2, JP153.3
VCC16: J65.2, J66.2, J67.2, J68.2, JP161.3V3, JP161.24, JP162.2, JP163.1, JP163.2, JP163.3
VCC17: J69.2, J70.2, J71.2, J72.2, JP171.3V3, JP171.24, JP172.2, JP173.1, JP173.2, JP173.3
VIN: JP1.1, JP1.VIN
VIN1: JP11.1, JP11.VIN
VIN2: JP21.1, JP21.VIN
VIN3: JP31.1, JP31.VIN
VIN4: JP41.1, JP41.VIN
VIN5: JP51.1, JP51.VIN
VIN6: JP61.1, JP61.VIN
VIN7: JP71.1, JP71.VIN
VIN8: JP81.1, JP81.VIN
VIN9: JP91.1, JP91.VIN
VIN10: JP101.1, JP101.VIN
VIN11: JP111.1, JP111.VIN
VIN12: JP121.1, JP121.VIN
VIN13: JP131.1, JP131.VIN
VIN14: JP141.1, JP141.VIN
VIN15: JP151.1, JP151.VIN
VIN16: JP161.1, JP161.VIN
VIN17: JP171.1, JP171.VIN
WKP: JP1.5, JP1.WKP
WKP1: JP11.5, JP11.WKP
WKP2: JP21.5, JP21.WKP
WKP3: JP31.5, JP31.WKP
WKP4: JP41.5, JP41.WKP
WKP5: JP51.5, JP51.WKP
WKP6: JP61.5, JP61.WKP
WKP7: JP71.5, JP71.WKP
WKP8: JP81.5, JP81.WKP
WKP9: JP91.5, JP91.WKP
WKP10: JP101.5, JP101.WKP
WKP11: JP111.5, JP111.WKP
WKP12: JP121.5, JP121.WKP
WKP13: JP131.5, JP131.WKP
WKP14: JP141.5, JP141.WKP
WKP15: JP151.5, JP151.WKP
WKP16: JP161.5, JP161.WKP
WKP17: JP171.5, JP171.WKP

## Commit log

2017-09-05 ran checklist, pre design review
2017-09-19 updated version silk, added gnd stitching
2017-09-19 panel
2017-11-27 Cleaned repo, fixed readme

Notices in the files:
parts and their libraries:
SparkFun-Aesthetics: Licensing: Creative Commons ShareAlike 4.0 International - https://creativecommons.org/licenses/by-sa/4.0
SparkFun-Aesthetics: Released under the Creative Commons Attribution Share-Alike 4.0 License
SparkFun-Aesthetics: https://creativecommons.org/licenses/by-sa/4.0
